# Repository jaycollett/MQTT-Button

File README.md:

# MQTT-Button

Simple MQTT based dual button device. For all the details on this project, head over to my blog. 

https://www.jaycollett.com/2019/03/a-simple-dual-mqtt-button/

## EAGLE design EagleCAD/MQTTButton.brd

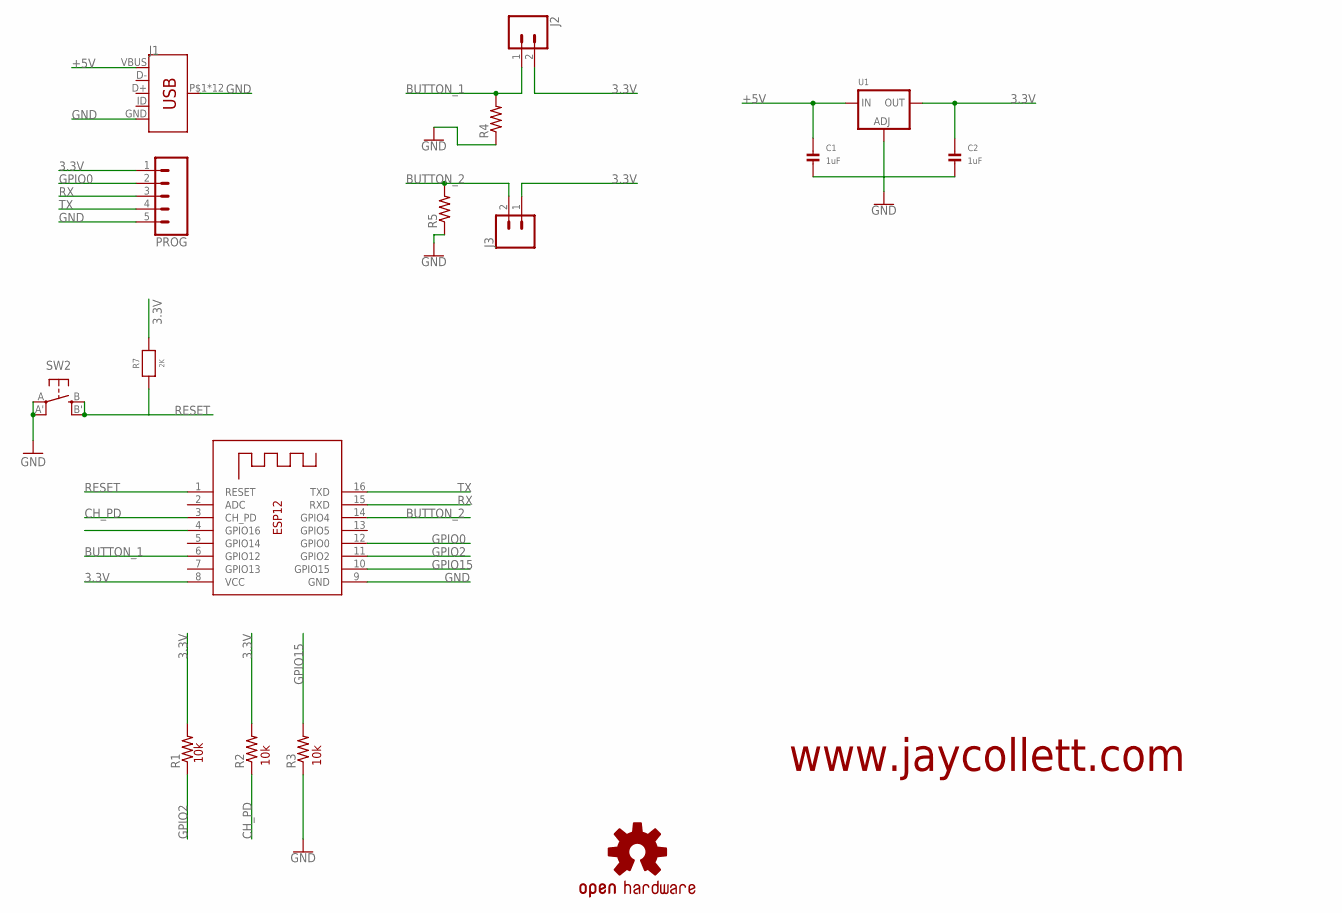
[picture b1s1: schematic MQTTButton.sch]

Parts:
C1, C2: 1uF; 0805
J1: USB_MICRO-B_HALF_PTH; USB-MICROB-PTH
J2, J3: CONN_02LOCK; 1X02_LOCK
LOGO1: OSHW-LOGOMINI; OSHW-LOGO-MINI
PROG: CONN_05; 1X05
R1, R2, R3, R4, R5: 10k; M0805
R7: 2K; 0805-NO
SW2: SPST_TACT-EVQQ2; EVQ-Q2
U1: LM1117SOT223-WAVE; SOT223-W
X1: ESP-12

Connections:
3.3V: C2.1, J2.2, J3.1, PROG.1, R1.2, R2.2, R7.2, U1.2 (OUT), X1.8 (VCC)
+5V: C1.1, J1.VBUS, U1.3 (IN)
BUTTON_1: J2.1, R4.2, X1.6 (GPIO12)
BUTTON_2: J3.2, R5.2, X1.14 (GPIO4)
CH_PD: R2.1, X1.3 (CH_PD)
GND: C1.2, C2.2, J1.GND, J1.P$1 (SHIELD), J1.P$2 (SHIELD), J1.P$3 (SHIELD), J1.P$4 (SHIELD), J1.P$6 (SHIELD), J1.P$8 (SHIELD), J1.P$10 (SHIELD), J1.P$12 (SHIELD), J1.SHEILD2 (SHIELD), J1.SHIELD, J1.SHIELD3 (SHIELD), J1.SHIELD4 (SHIELD), PROG.5, R3.1, R4.1, R5.1, SW2.A, SW2.A' (P1), U1.1 (ADJ), X1.9 (GND)
GPIO0: PROG.2, X1.12 (GPIO0)
GPIO2: R1.1, X1.11 (GPIO2)
GPIO15: R3.2, X1.10 (GPIO15)
RESET: R7.1, SW2.B (S), SW2.B' (S1), X1.1 (RESET)
RX: PROG.3, X1.15 (RXD)
TX: PROG.4, X1.16 (TXD)

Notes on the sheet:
10k
www.jaycollett.com

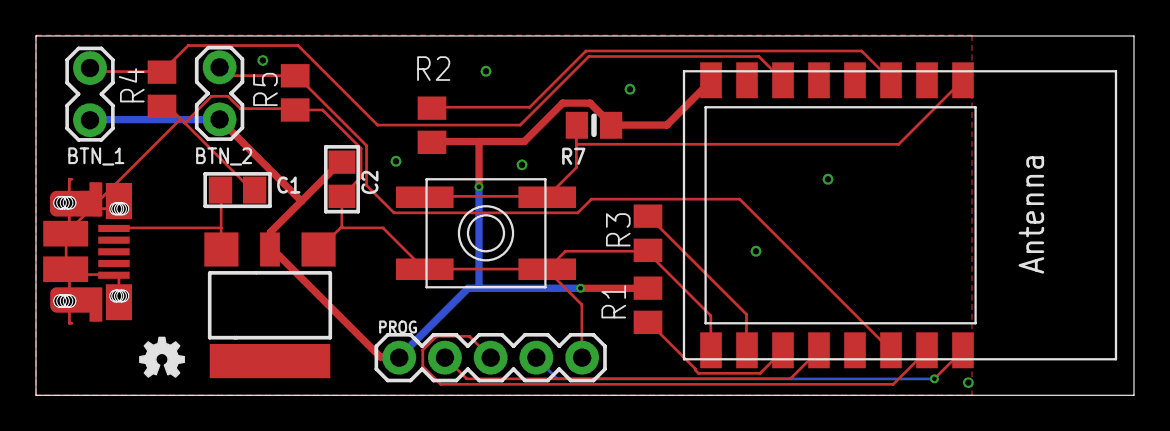
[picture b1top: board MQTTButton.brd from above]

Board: 2 copper layers, 61.0 x 20.0 mm, 16 parts (0 on the bottom side), 12 nets.

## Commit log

2019-02-12 Initial board layout and schematic. Sent to OSHPark.com
2019-02-19 inital draft design for bottom of enclosure
2019-02-19 tweaks to bottom
2019-02-22 added top of enclosure, tweaked bottom to add screw hole supports
2019-02-23 added additional mount towers to bottom, wasn't happen with how it was secured.
2019-02-23 updated design to include pull-down resistors on button input lines
2019-02-23 added updated images for schematic and board
2019-02-24 tweaking bottom board holder after getting PCBs.
2019-02-24 tweaked top based on tweaks to bottom.
2019-02-24 fixed usb connector, rerouted
2019-02-24 tweaked location of board stopper tab
2019-03-08 first pass at firmware
2019-03-08 updating firmware
2019-03-08 updated firmware to simple on and off states
2019-03-08 swapped button values
2019-03-08 adding project image files
2021-01-09 Add travis ci support and update readme
2021-01-09 Update MQTT-Button.ino
    remove unused callback code.

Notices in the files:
parts and their libraries:
microbuilder: This work is placed in the public domain, and may be freely used for commercial and non-commercial work with the following conditions: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
SparkFun-Connectors: Licensing: Creative Commons ShareAlike 4.0 International - https://creativecommons.org/licenses/by-sa/4.0
